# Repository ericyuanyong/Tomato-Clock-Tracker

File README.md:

# Tomato Clock Tracker 🍅

## Background

This is a small personal project that records Pomodoro (tomato clock) sessions using a 
[Particle P2](https://store.particle.io/products/p2) device and a 
[Particle Tachyon](https://store.particle.io/products/tachyon) backend.
> *"Knowledge is not free --- you have to pay attention."*

In today's world, it is becoming harder to stay focused. We are
surrounded by smart devices, notifications, and endless streams of
distraction.

At the beginning of **2026**, I decided to take my attention back.\
So I built my own **physical tomato clock**.

The idea is simple:\
when I want to focus, I press a button and commit to **30 minutes of
uninterrupted work**.

------------------------------------------------------------------------

## Features

This project intentionally keeps things simple.\
It has **only two features**:

1.  **Start a 30-minute focus session** by pressing a button.
2.  **Receive a daily email report** showing how many focus sessions
    were completed.

That's it. No apps, no notifications, no distractions.

------------------------------------------------------------------------

## System Architecture

To keep the design simple:

-   **Particle P2** acts as the local controller.
-   **Tachyon** acts as the backend subscriber.

```
    Button press
        ↓
    Particle P2
        ↓
    Particle Cloud (event publish)
        ↓
    Tachyon subscriber
        ↓
    SQLite database
        ↓
    Weekly report script (cron)
        ↓
    Email summary
```

### Components

**Device** - Particle **P2** - Button input - Optional LCD / progress
bar display

**Backend** - Tachyon - Python scripts - SQLite
database - Cron scheduler

------------------------------------------------------------------------

## Reporting

One feature that distinguishes this tomato clock from others is the
**daily email report**.

Every day I receive an email summarizing:

-   total focus sessions
-   total focus time
-   daily breakdown

Example report:

    🍅 Tomato Clock Weekly Report

    Total sessions: 66
    Focus time: 1980 minutes

    Daily breakdown (Mon → Sun):

    Mon | ████                 8
    Tue | ███████              14
    Wed | ███████████          23
    Thu | ███████████████      31
    Fri | ██                   4
    Sat |                      0
    Sun |                      0

> 💡 **Motivation**  
> Checking this report has become a small reward that motivates me to keep improving my focus.

------------------------------------------------------------------------

## Repository Structure

    tomato_clock/
    │
    ├── subscriber.py
    ├── report_and_email.py
    ├── requirements.txt
    ├── tomato.db
    ├── report.log
    └── README.md

------------------------------------------------------------------------

## Requirements

Python 3.10+

Install dependencies:

``` bash
pip install -r requirements.txt
```

Typical dependencies:

    requests
    sseclient-py
    matplotlib

------------------------------------------------------------------------

## Running the Subscriber

The subscriber listens to **Particle Cloud events** and writes them into
the SQLite database.

Run manually:

``` bash
python subscriber.py
```

Recommended: run as a **systemd service**.

------------------------------------------------------------------------

## Scheduling the Report

Use **cron** to send the daily/weekly email report.

Edit crontab:

``` bash
crontab -e
```

Example (Friday 18:00):

``` bash
0 18 * * FRI /home/eric/myvenv/bin/python /home/eric/tomato_clock/report_and_email.py >> /home/eric/tomato_clock/report.log 2>&1
```

------------------------------------------------------------------------

## Limitations

Most of the backend code in this project was developed with the help of
**ChatGPT**.

The most difficult part was configuring **SMTP email sending on the
Tachyon**, especially when working with providers like Outlook or
Gmail.

------------------------------------------------------------------------

## Author

Eric Yuan\
ChatGPT

------------------------------------------------------------------------

## Motivation

This project is not about building a complicated productivity tool.

It is about something much simpler:

> **Take back control of attention.**

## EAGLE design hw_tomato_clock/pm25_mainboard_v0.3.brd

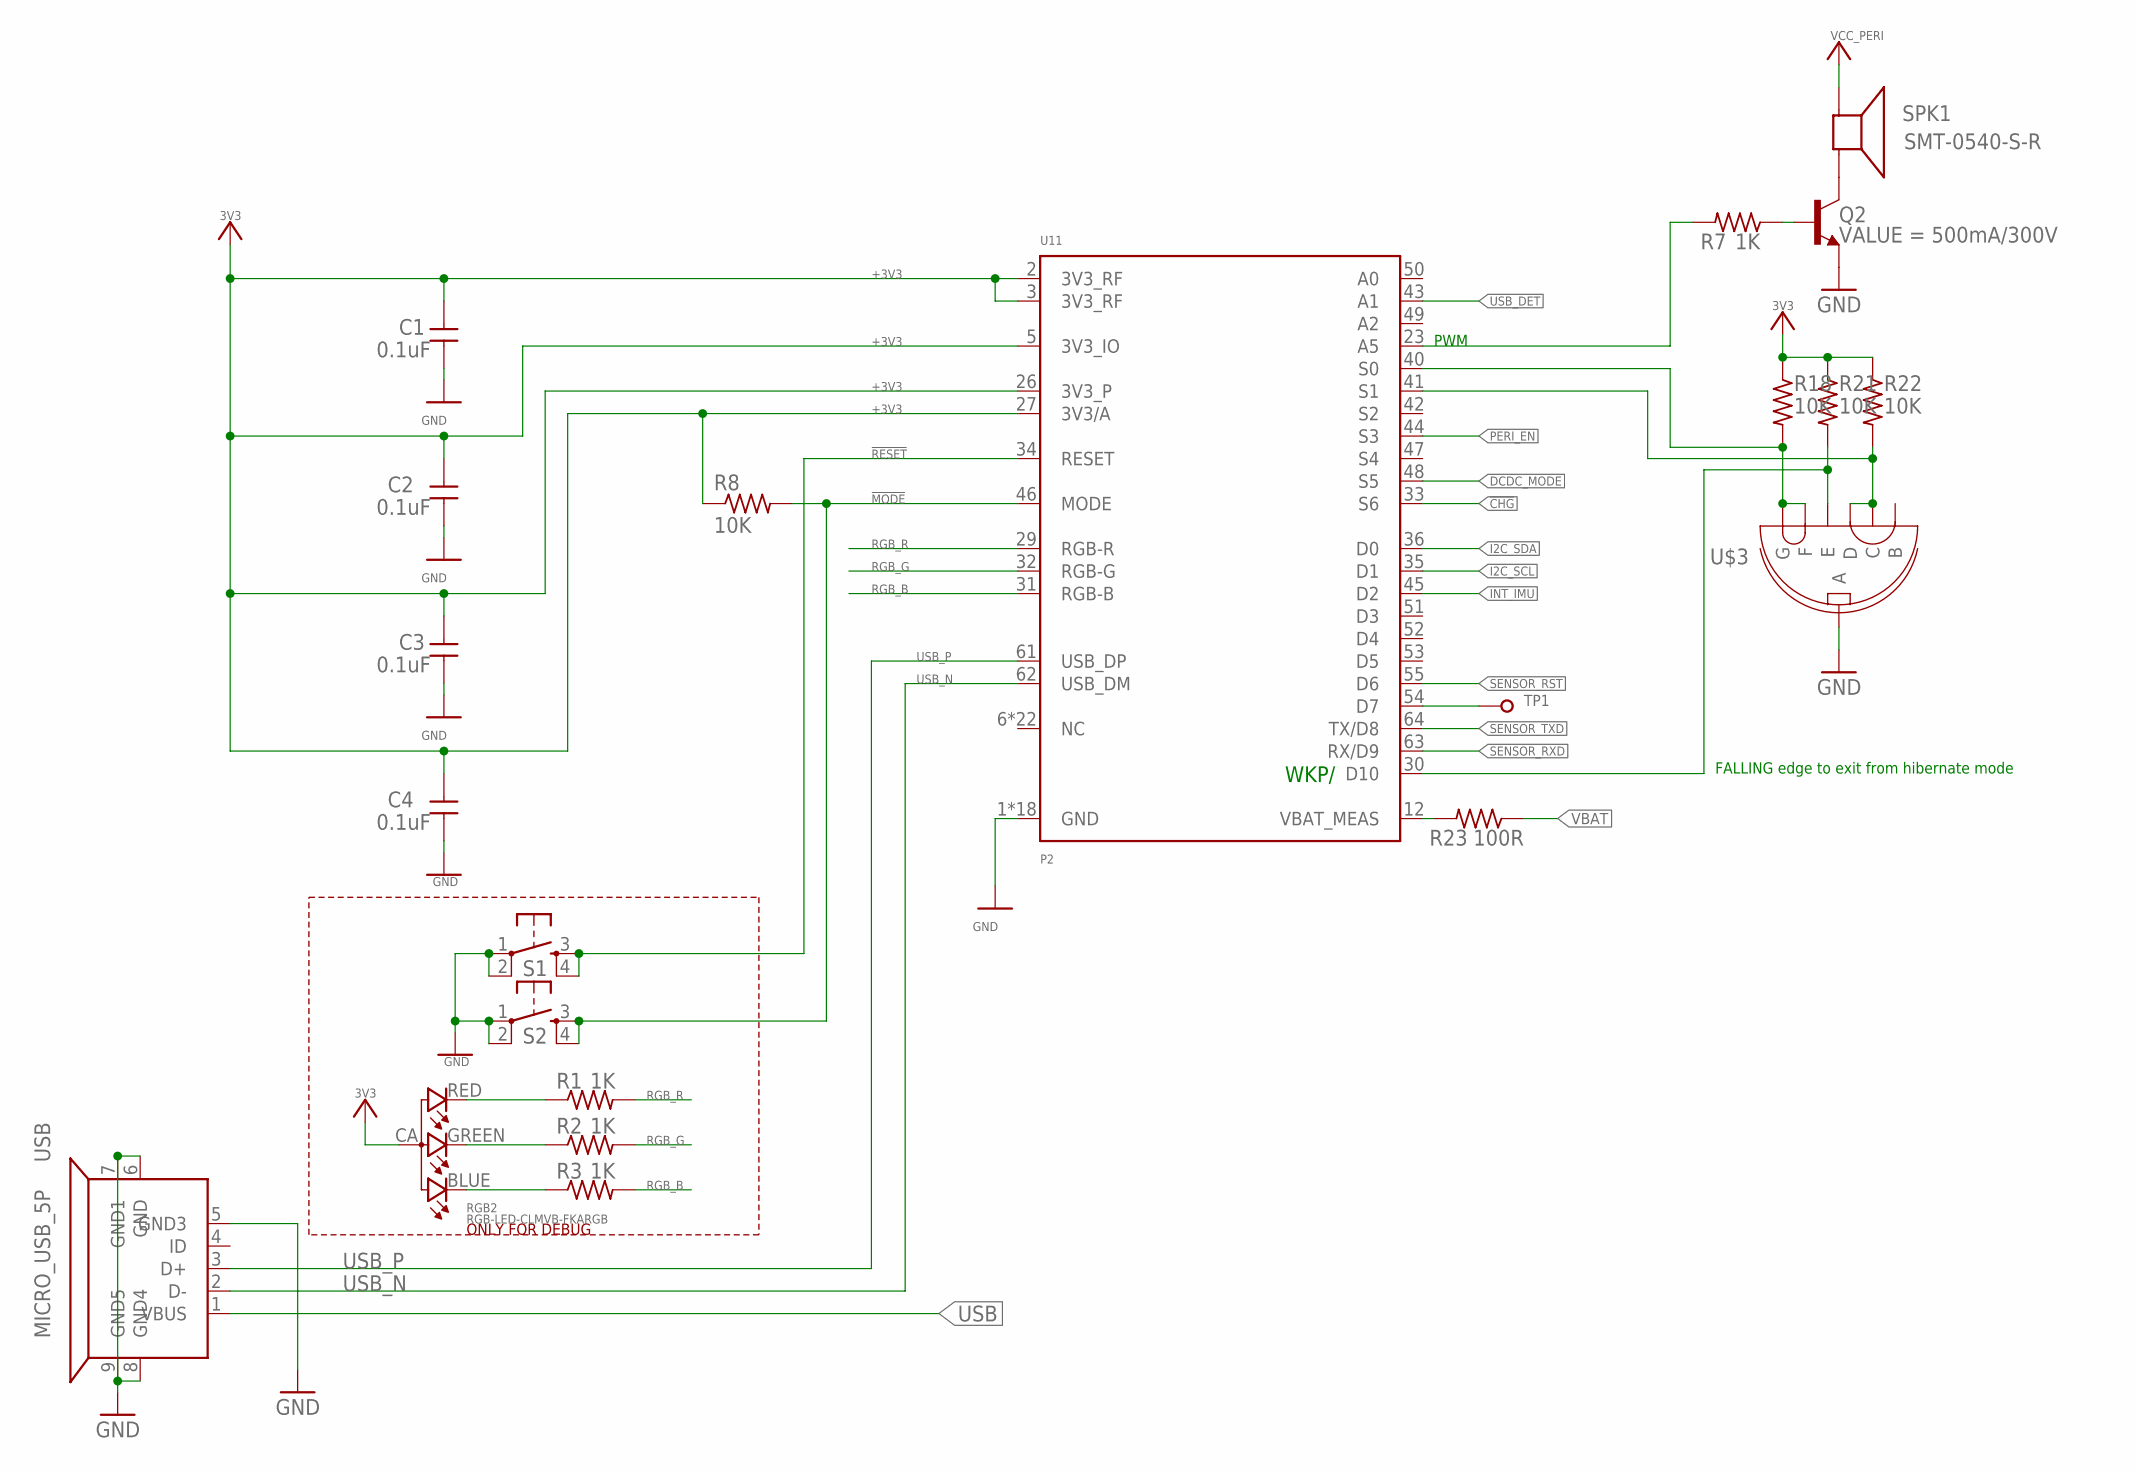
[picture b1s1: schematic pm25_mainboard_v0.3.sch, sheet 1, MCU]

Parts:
C1, C2, C3, C4: 0.1uF; C0603_P
Q2: 500mA/300V; SOT23-3; MPN MMBTA42-7-F
R1, R2, R3: 1K; R0603_P
R7: 1K; R0603_P; MPN RC-03K102FT
R8, R18, R21, R22: 10K; R0603_P
R23: 100R; R0603_P
RGB2: RGB-LED-CLMVB-FKARGB; PLCC4-2MM-RGB
S1, S2: TAC_SWITCHSMD; TACTILE_SWITCH_SMD
SPK1: SMT-0540-S-R; MPN SMT-0540-S-R
TP1: TP-1.5MM; TP
U11: P2
U$3: MULTI_FUN_SWITCH
USB: MICRO_USB_5P; MICRO_USB

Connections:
!CHG: U11.33 (S6); also elsewhere on the board
!MODE: R8.2, S2.3, S2.4, U11.46 (MODE)
!RESET: S1.3, S1.4, U11.34 (RESET)
+3V3: C1.1, C2.1, C3.1, C4.1, R8.1, R18.1, R21.1, R22.1, RGB2.CA (1), U11.2 (3V3_RF), U11.3 (3V3_RF), U11.5 (3V3_IO), U11.26 (3V3_P), U11.27 (3V3/A); also elsewhere on the board
BUZZER: R7.2, U11.23 (A5)
DCDC_MODE: U11.48 (S5); also elsewhere on the board
GND: C1.2, C2.2, C3.2, C4.2, Q2.2 (E), S1.1, S1.2, S2.1, S2.2, U11.1 (GND), U11.4 (GND), U11.13 (GND), U11.15 (GND), U11.25 (GND), U11.28 (GND), U11.37 (GND), U11.39 (GND), U11.59 (GND), U11.65 (GND), U11.66 (GND), U11.67 (GND), U11.68 (GND), U11.69 (GND), U11.70 (GND), U11.71 (GND), U11.72 (GND), U11.73 (GND), U$3.A, USB.5 (GND3), USB.6 (GND), USB.7 (GND1), USB.8 (GND4), USB.9 (GND5); also elsewhere on the board
I2C_SCL: U11.35 (D1); also elsewhere on the board
I2C_SDA: U11.36 (D0); also elsewhere on the board
INT_IMU: U11.45 (D2); also elsewhere on the board
LEFT: R22.2, U11.41 (S1), U$3.C, U$3.D
MID: R21.2, U11.30 (D10), U$3.E
unnamed: Q2.3 (C), SPK1.- (+)
unnamed: R23.2, U11.12 (VBAT_MEAS)
unnamed: TP1.TP, U11.54 (D7)
unnamed: R1.1, RGB2.RED (4)
unnamed: R2.1, RGB2.GREEN (3)
unnamed: R3.1, RGB2.BLUE (2)
unnamed: Q2.1 (B), R7.1
PERI_EN: U11.44 (S3); also elsewhere on the board
RGB_B: R3.2, U11.31 (RGB-B)
RGB_G: R2.2, U11.32 (RGB-G)
RGB_R: R1.2, U11.29 (RGB-R)
RIGHT: R18.2, U11.40 (S0), U$3.F, U$3.G
SENSOR_RST: U11.55 (D6); also elsewhere on the board
SENSOR_RXD: U11.63 (RX/D9); also elsewhere on the board
SENSOR_TXD: U11.64 (TX/D8); also elsewhere on the board
USB: USB.1 (VBUS); also elsewhere on the board
USB_DET: U11.43 (A1); also elsewhere on the board
USB_N: U11.62 (USB_DM), USB.2 (D-)
USB_P: U11.61 (USB_DP), USB.3 (D+)
VBAT: R23.1; also elsewhere on the board
VCC_PERI: SPK1.+ (-); also elsewhere on the board

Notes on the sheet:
ONLY FOR DEBUG
WKP/
PWM
FALLING edge to exit from hibernate mode

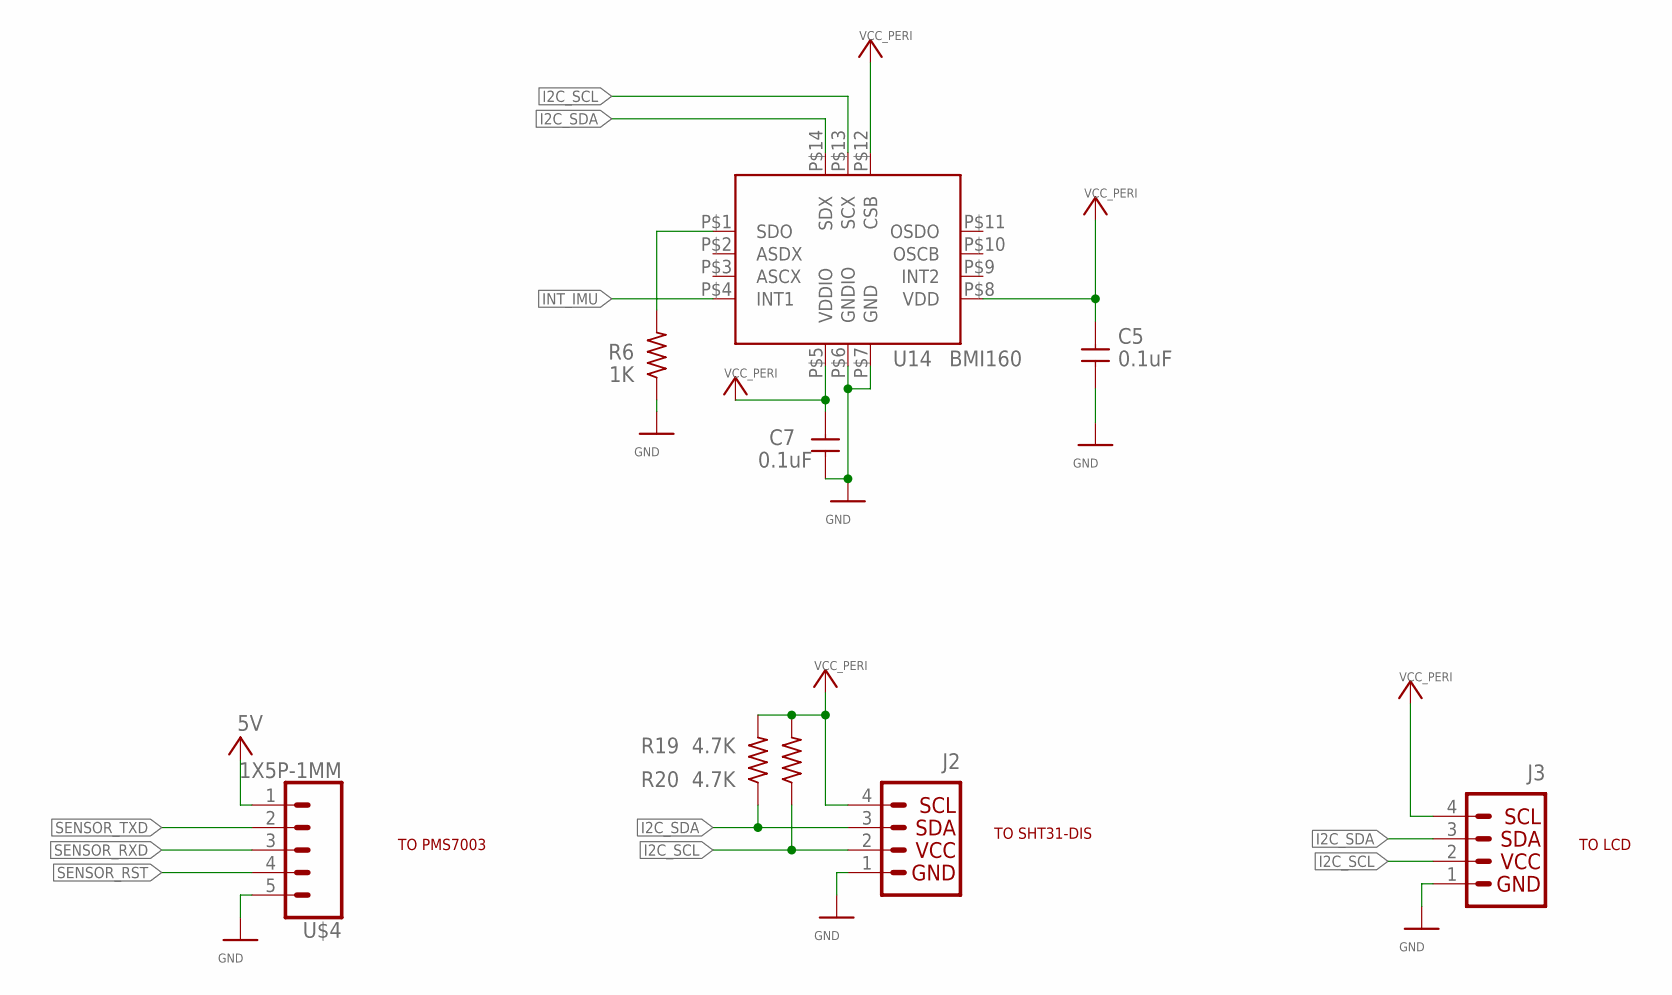
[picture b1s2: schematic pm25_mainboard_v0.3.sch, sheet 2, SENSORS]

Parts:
C5, C7: 0.1uF; C0603_P
J2, J3: QWIIC_CONNECTORJS-1MM; 1X04_1MM_RA
R6: 1K; R0603_P
R19, R20: 4.7K; R0603_P
U14: BMI160; LGA-14L
U$4: 1X5P-1MM; 1X05-1MM

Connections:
5V: U$4.1; also elsewhere on the board
GND: C5.2, C7.2, J2.1 (GND), J3.1 (GND), R6.1, U14.P$6 (GNDIO), U14.P$7 (GND), U$4.5; also elsewhere on the board
I2C_SCL: J2.2 (VCC), J3.2 (VCC), R20.1, U14.P$13 (SCX); also elsewhere on the board
I2C_SDA: J2.3 (SDA), J3.3 (SDA), R19.1, U14.P$14 (SDX); also elsewhere on the board
INT_IMU: U14.P$4 (INT1); also elsewhere on the board
unnamed: R6.2, U14.P$1 (SDO)
SENSOR_RST: U$4.4; also elsewhere on the board
SENSOR_RXD: U$4.3; also elsewhere on the board
SENSOR_TXD: U$4.2; also elsewhere on the board
VCC_PERI: C5.1, C7.1, J2.4 (SCL), J3.4 (SCL), R19.2, R20.2, U14.P$5 (VDDIO), U14.P$8 (VDD), U14.P$12 (CSB); also elsewhere on the board

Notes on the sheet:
TO PMS7003
TO SHT31-DIS
TO LCD

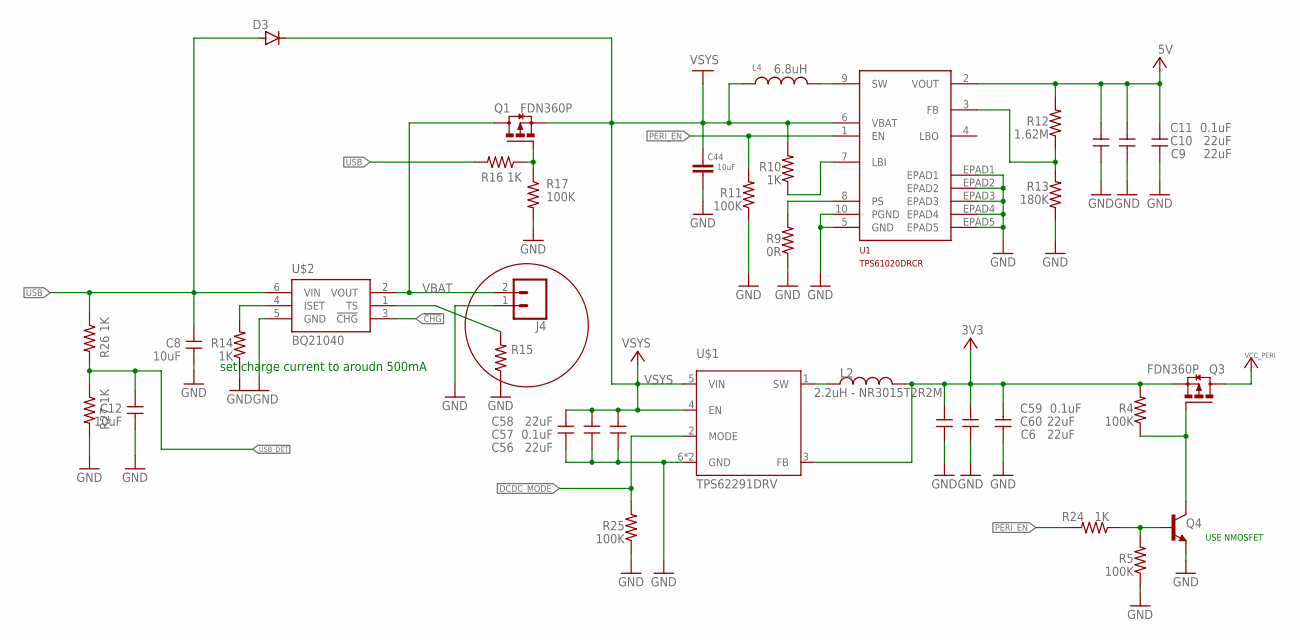
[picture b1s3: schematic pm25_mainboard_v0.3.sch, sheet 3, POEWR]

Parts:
C6, C10, C11, C56, C58, C60: 22uF; C0603_P
C8, C12: 10uF; C0603_P
C9, C57, C59: 0.1uF; C0603_P
C44: 10uF; C0805_MURATA_GRM21
D3: DIODE-SOD123; SOD123
J4: CONN_02-JST-2MM-SMT; JST-2-SMD
L2: 2.2uH - NR3015T2R2M; INDUCTOR-NR3015; MPN NR3015T2R2M
L4: 6.8uH; CDRH5D28NP-6R2NC
Q1, Q3: FDN360P; SUPER-SOT3
Q4: TRANS_NPN-MMBTA42; SOT23-3; MPN MMBTA42-7-F
R4, R5, R11, R17, R25: 100K; R0603_P
R9: 0R; R0603_P
R10, R14, R16, R24, R26, R27: 1K; R0603_P
R12: 1.62M; R0603_P
R13: 180K; R0603_P
R15: RES_0603; R0603_P
U1: TPS61020DRCR
U$1: TPS62291DRV; S-PWSON-N6
U$2: BQ21040; SOT23-6

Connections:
3V8_SW: L4.P$2 (2), U1.9 (SW)
5V: C9.2, C10.2, C11.2, R12.2, U1.2 (VOUT); also elsewhere on the board
!CHG: U$2.3 (!CHG); also elsewhere on the board
+3V3: C6.2, C59.2, C60.2, L2.2, Q3.2 (S), R4.2, U$1.3 (FB); also elsewhere on the board
DCDC_MODE: R25.2, U$1.2 (MODE); also elsewhere on the board
GND: C6.1, C8.1, C9.1, C10.1, C11.1, C12.1, C44.2, C56.1, C57.1, C58.1, C59.1, C60.1, J4.1 (2), Q4.2 (E), R5.1, R9.1, R11.1, R13.1, R14.1, R15.1, R17.2, R25.1, R27.2, U1.5 (GND), U1.10 (PGND), U1.EPAD1, U1.EPAD2, U1.EPAD3, U1.EPAD4, U1.EPAD5, U$1.6 (GND), U$1.TP (GND), U$2.5 (GND); also elsewhere on the board
unnamed: R9.2, U1.8 (PS)
unnamed: R10.1, U1.7 (LBI)
unnamed: R14.2, U$2.4 (ISET)
unnamed: R12.1, R13.2, U1.3 (FB)
unnamed: Q3.1 (G), Q4.3 (C), R4.1
unnamed: R15.2, U$2.1 (TS)
unnamed: Q1.1 (G), R16.1, R17.1
unnamed: Q4.1 (B), R5.2, R24.1
unnamed: L2.1, U$1.1 (SW)
PERI_EN: R11.2, R24.2, U1.1 (EN); also elsewhere on the board
USB: C8.2, D3.A, R16.2, R26.1, U$2.6 (VIN); also elsewhere on the board
USB_DET: C12.2, R26.2, R27.1; also elsewhere on the board
VBAT: J4.2 (1), Q1.3 (D), U$2.2 (VOUT); also elsewhere on the board
VCC_PERI: Q3.3 (D); also elsewhere on the board
VSYS: C44.1, C56.2, C57.2, C58.2, D3.C, L4.P$1 (1), Q1.2 (S), R10.2, U1.6 (VBAT), U$1.4 (EN), U$1.5 (VIN)

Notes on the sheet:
USE NMOSFET
set charge current to aroudn 500mA

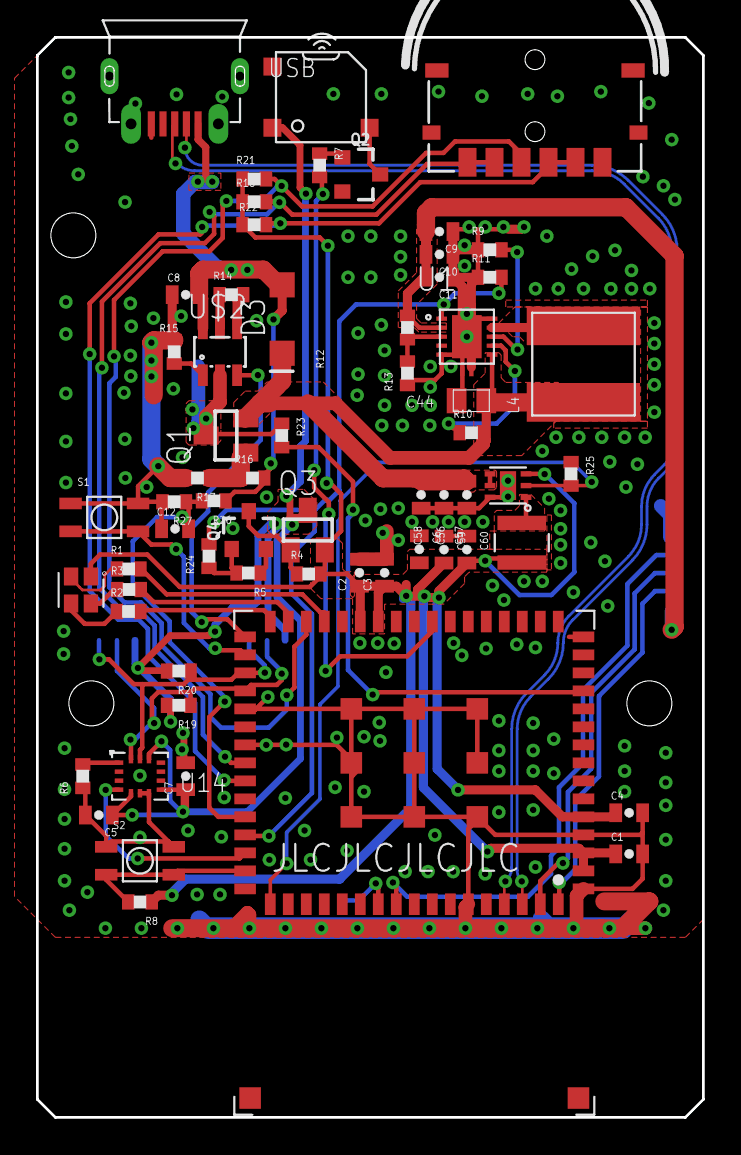
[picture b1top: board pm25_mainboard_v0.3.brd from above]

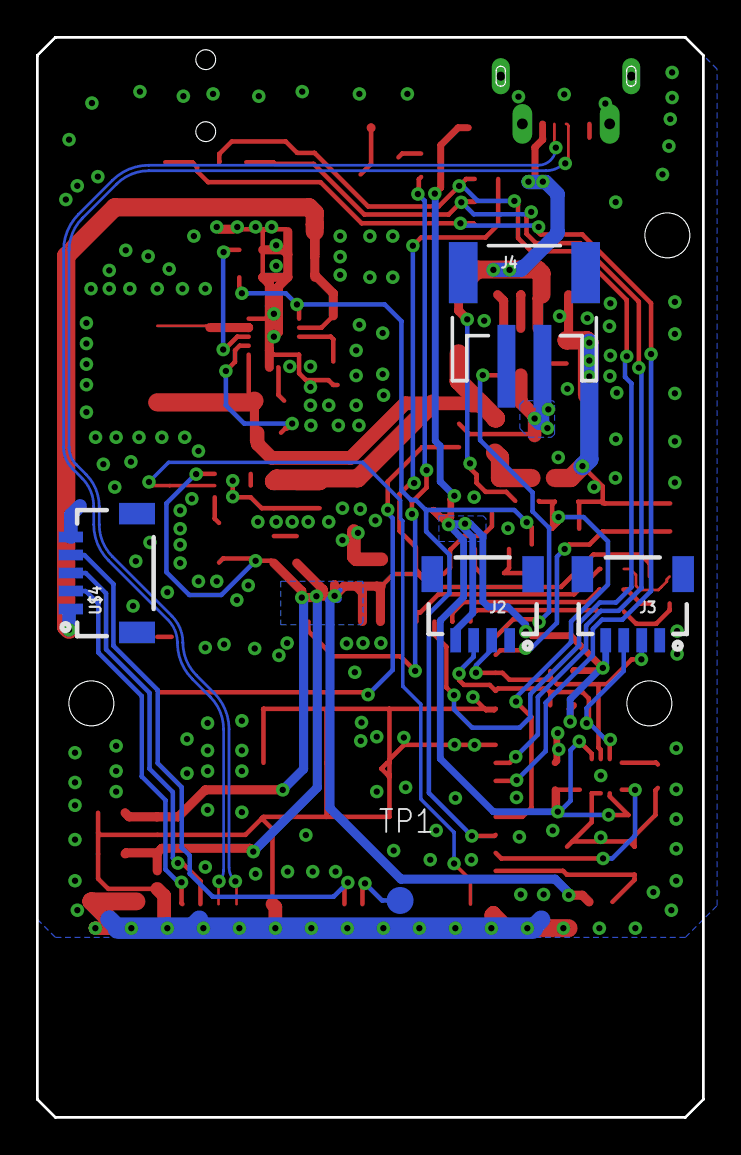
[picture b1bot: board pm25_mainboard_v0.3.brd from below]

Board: 2 copper layers, 37.0 x 60.0 mm, 68 parts (5 on the bottom side), 46 nets.

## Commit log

2026-03-10 put the fw and script into the folder
2026-03-16 move hw file into this repository

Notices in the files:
parts and their libraries:
SparkFun-Connectors: Licensing: Creative Commons ShareAlike 4.0 International - https://creativecommons.org/licenses/by-sa/4.0
